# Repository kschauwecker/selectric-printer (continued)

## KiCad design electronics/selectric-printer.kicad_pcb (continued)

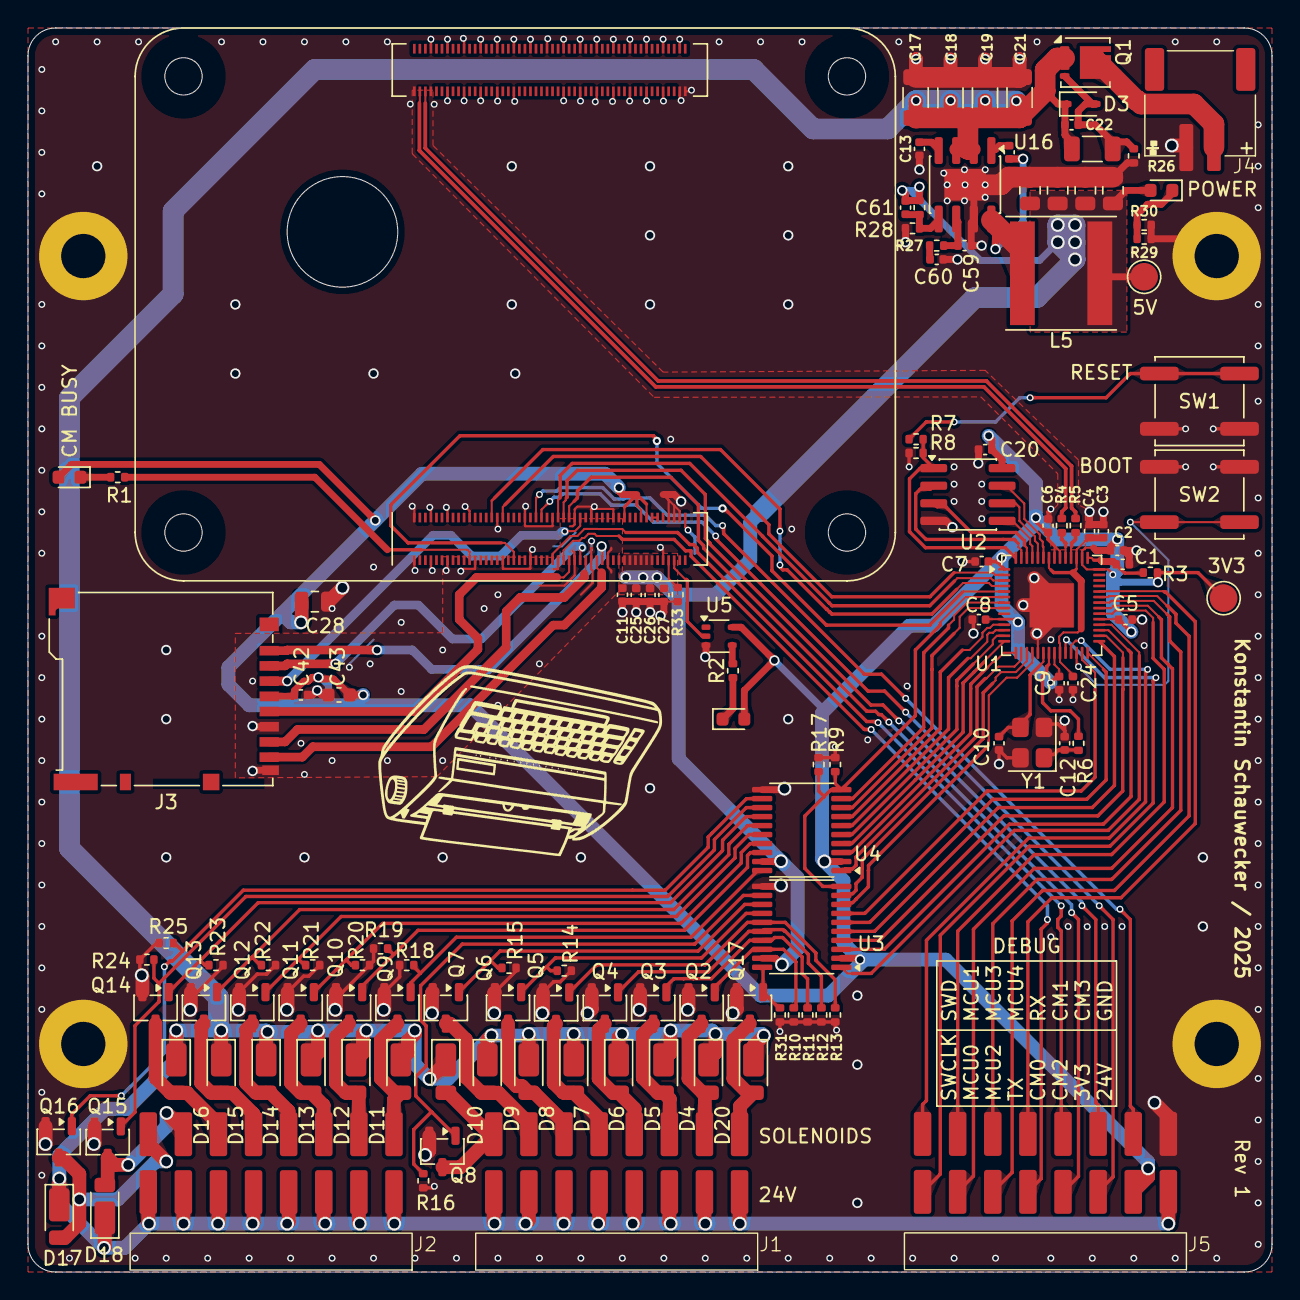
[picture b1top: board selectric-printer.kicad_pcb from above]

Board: 2 copper layers, 90.0 x 90.0 mm, 128 parts (1 on the bottom side), 110 nets.

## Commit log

2025-12-01 Initial commit of electronics design
